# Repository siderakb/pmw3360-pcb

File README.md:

# PMW3360 PCB

| 2.54mm Pin Header                                                                                     | 0.5mm FFC/FPC                                                                                         |
| ----------------------------------------------------------------------------------------------------- | ----------------------------------------------------------------------------------------------------- |
|  |  |

[PixArt PMW3360DM-T2QU](https://www.pixart.com/products-detail/10/PMW3360DM-T2QU) optical mouse sensor breakout board, can be operated with either a 1.8V or 3.3V voltage level.  
Also look at [PMW3610 PCB](https://github.com/siderakb/pmw3610-pcb).

[Demo video 1](https://youtu.be/orrze81mV_8?t=312), [Demo video 2](https://youtu.be/CSA7Ih7nAls?si=umx-Psb8-lRDeviu)

## PCB

Online preview available [here](https://kicanvas.org/?github=https%3A%2F%2Fgithub.com%2Fsiderakb%2Fpmw3360-pcb%2Ftree%2Fmain%2Fpmw3360_pcb_pinheader), powered by [KiCanvas](https://github.com/theacodes/kicanvas).

### BOM

| Ref  | Value         | Footprint             |
| ---- | ------------- | --------------------- |
| C1   | 4.7uF/10V     | SMD 0603              |
| C2   | 100nF         | SMD 0603              |
| C3   | 1uF           | SMD 0603              |
| C4\* | 1uF           | SMD 0603              |
| C5\* | *DNI*         | SMD 0603              |
| R1\* | *DNI* or 10kΩ | SMD 0603              |
| R2   | 10kΩ          | SMD 0603              |
| R3   | 39Ω           | SMD 0603              |
| R4\* | *DNI*         | SMD 0603              |
| U1   | PMW3360       | PMW3360DM-T2QU 16 Pin |
| U2\* | TLV74318PDBVR | SOT-23-5              |
| J1\* | 8 Pin         |                       |

- *DNI*: don't install.
- SMD 0603 (Imperial) aka 1608 Metric.
- PMW3360 needs to be used with LM19-LSI lens.
- `R1` is optional/additional RESET pull up resistor, RESET pin of PMW3360 has a built in weak pull up circuit.
- `J1` connector have the following options:
    - 2.54mm pin header: [`pmw3360_pcb_pinheader/`](/pmw3360_pcb_pinheader/)
    - 0.5mm FFC/FPC: [`pmw3360_pcb_ffc/`](/pmw3360_pcb_ffc/)
    - JST GH 1.25mm: [`pmw3360_pcb_jst/`](/pmw3360_pcb_jst/)
- `U2` LDO regulator have the following options:

|  Ref  | Default       | Alt.           | Alt.        |
| :---: | ------------- | -------------- | ----------- |
|  U2   | TLV74318PDBVR | RT9193-18GB    | TPS73601DBV |
|  C4   | 1uF           | 1uF            | 4.7uF       |
|  C5   | *DNI*         | 22nF or larger | 56.2k**Ω**  |
|  R4   | *DNI*         | *DNI*          | 28kΩ        |
| Note  | Fixed 1.8V    | Fixed 1.8V     | Adj. 1.8V   |

### PCB Dimensions & Characteristics

Please refer to:
- 2.54mm pin header: [`pmw3360_pcb_pinheader/`](/pmw3360_pcb_pinheader/)
- 0.5mm FFC/FPC: [`pmw3360_pcb_ffc/`](/pmw3360_pcb_ffc/)
- JST GH 1.25mm: [`pmw3360_pcb_jst/`](/pmw3360_pcb_jst/)

> PCB sizes vary among different connector editions.

## Power

### Voltage-Level Config

3 configs available:

|          |   3.3V    |    1.8 with LDO     |         1.8V without LDO          |
| -------- | :-------: | :-----------------: | :-------------------------------: |
| VIN Typ. |   3.3V    | (VDD + 0.2V) ~ 5.5V |               1.8V                |
| VIN Max. |   3.6V    |        5.5V         |               2.1V                |
| JP1      | `[1-2 3]` |      `[1 2-3]`      |             `[1-2-3]`             |
| Note     |           |                     | `U2`, `R4`, `C3~5` can be omitted |

### Jumper

| JP1 Config |                     | Description                  |
| :--------: | ------------------- | ---------------------------- |
| `[1-2 3]`  | 2 and 1 close, 3 NC | VIO = VIN                    |
| `[1 2-3]`  | 2 and 3 close, 1 NC | VIO = VDD (i.e. LDO output)  |
| `[1-2-3]`  | 1, 2 and 3 close    | VIO = VDD = VIN (LDO bypass) |

### Operating Voltage Range

- **VDD**: 1.8 ~ 2.1V (i.e. LDO Vout)
- **VIO**: VDD ~ 3.6V (i.e. VDDIO)
- **VIN**: Depends on [Voltage-Level config](#voltage-level-config)

## Firmware Examples

- QMK
    - [RP2040](/firmware/qmk/pmw3360_rp2040/)
    - [Pro Micro](/firmware/qmk/pmw3360_promicro/)
- [nRF Connect SDK (NCS)](/firmware/nordic/)

Pre-Build firmware can be found in [Releases](https://github.com/siderakb/pmw3360-pcb/releases/tag/fw_v0.1.0).

## License

- KiCad files (e.g. schematics, PCBs, footprints and symbols): [CERN-OHL-P v2](/LICENSE-CERN-OHL-P).
- `firmware/qmk/`: [GPL v2](/LICENSE-QMK).
- `firmware/nordic/`: [Nordic-5-Clause](/LICENSE-Nordic).

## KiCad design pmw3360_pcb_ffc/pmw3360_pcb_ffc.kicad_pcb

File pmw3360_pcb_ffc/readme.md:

# PMW3360 PCB FFC/FPC Connector

- `J1`: 0.5mm 8pin FFC/FPC connector (AFC01-S08FCA-00).
- Mounting holes: 4x M2 (∅2.2mm).

## PCB Characteristics

- Copper layer count: 2
- Board overall dimensions: 27 mm x 22.5 mm
- Min track/spacing: 0.2 mm / 0.2 mm
- Min hole diameter: 0.3 mm
- Castellated pads: No
- Plated board edge: No
- Edge card connectors: No

## Changelog

### [F.1.0] - 2023-12-15

- Changed LDO from TPS73601DBV to TLV74318PDBVR.
- Changed R5 to C5.

### [F.0.0] - 2023-06-29

- Reduce the board size to 27 x 22.5 mm.
- Update PWM3360 footprint (reduce the size of the pads).

### [3.1.0] - 2023-05-27

- First FFC/FPC edition release.

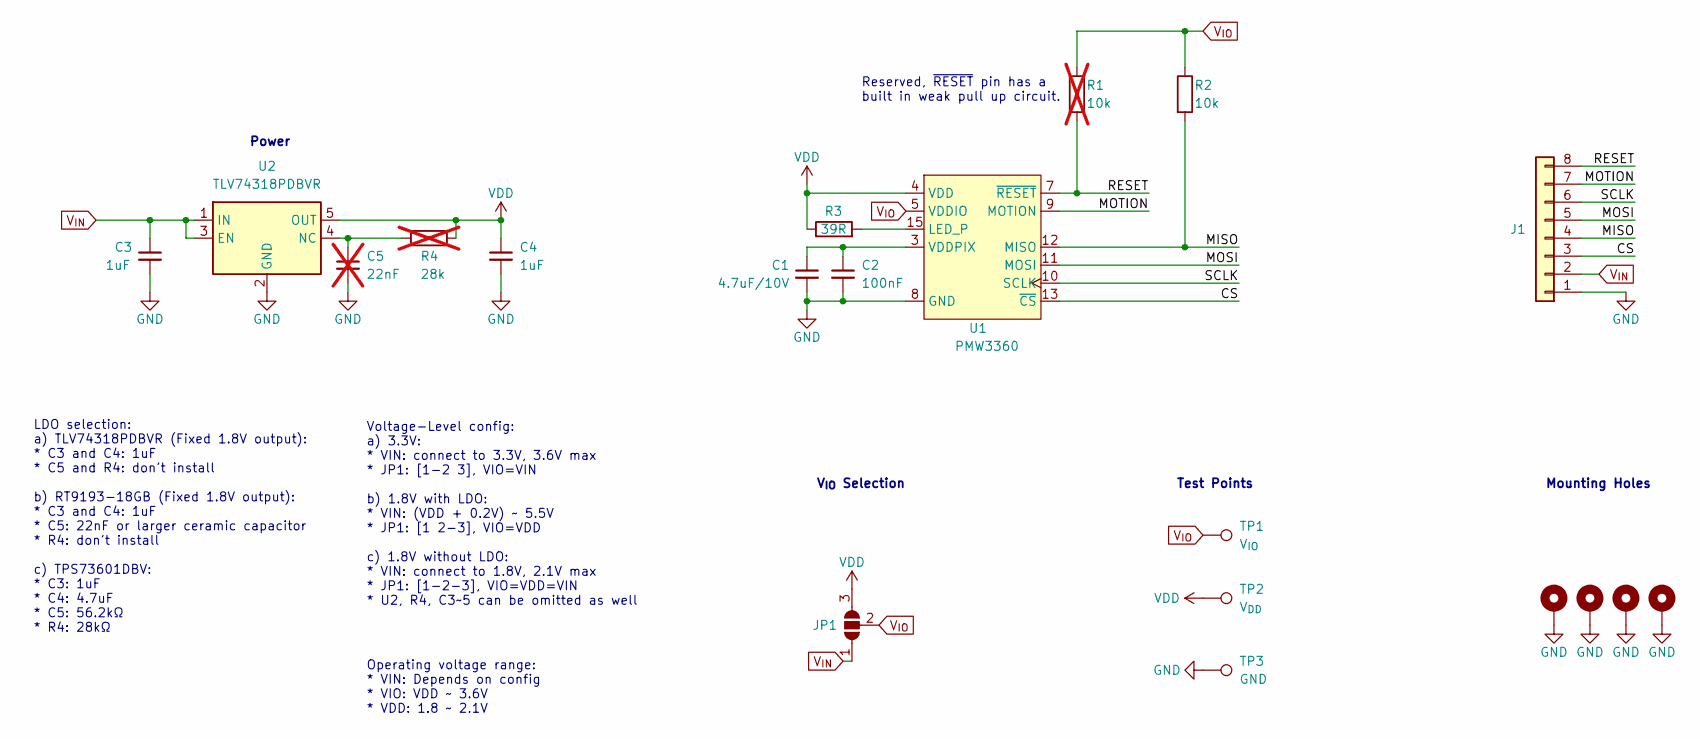
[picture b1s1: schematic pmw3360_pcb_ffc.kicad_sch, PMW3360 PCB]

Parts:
C1: 4.7uF/10V; C_0603_1608Metric_Pad1.08x0.95mm_HandSolder
C2: 100nF; C_0603_1608Metric_Pad1.08x0.95mm_HandSolder
C3, C4: 1uF; C_0603_1608Metric_Pad1.08x0.95mm_HandSolder
C5: 22nF; C_0603_1608Metric_Pad1.08x0.95mm_HandSolder; Mfr. # CL10B223KB8NNNC; LCSC C21122; not fitted
H1, H2, H3, H4: MountingHole_Pad; MountingHole_2.2mm_M2_ISO14580_Pad
J1: Interface; FPC_8P_0.5mm_AFC01-S08FCA-00
JP1: SolderJumper_3_Open; SolderJumper-3_P1.3mm_Open_RoundedPad1.0x1.5mm_NumberLabels
R1: 10k; R_0603_1608Metric_Pad0.98x0.95mm_HandSolder; not fitted
R2: 10k; R_0603_1608Metric_Pad0.98x0.95mm_HandSolder
R3: 39R; R_0603_1608Metric_Pad0.98x0.95mm_HandSolder
R4: 28k; R_0603_1608Metric_Pad0.98x0.95mm_HandSolder; not fitted
TP1: V_{IO}; TestPoint_Pad_D1.0mm
TP2: V_{DD}; TestPoint_Pad_D1.0mm
TP3: GND; TestPoint_Pad_D1.0mm
U1: PMW3360; PMW3360DM-T2QU 16Pin
U2: TLV74318PDBVR; SOT-23-5; Mfr. # TLV74318PDBVR; LCSC C485152

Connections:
/CS: J1.3, U1.13 (~CS)
/MISO: J1.4, R2.2, U1.12 (MISO)
/MOSI: J1.5, U1.11 (MOSI)
/MOTION: J1.7, U1.9 (MOTION)
/RESET: J1.8, R1.2, U1.7 (~RESET)
/SCLK: J1.6, U1.10 (SCLK)
GND: C1.2, C2.2, C3.2, C4.2, C5.2, H1.1, H2.1, H3.1, H4.1, J1.1, TP3.1, U1.8 (GND), U2.2 (GND)
unnamed: R3.2, U1.15 (LED_P)
unnamed: C1.1, C2.1, U1.3 (VDDPIX)
unnamed: C5.1, R4.2, U2.4 (NC)
VDD: C4.1, JP1.3 (B), R3.1, R4.1, TP2.1, U1.4 (VDD), U2.5 (OUT)
V_{IN}: C3.1, J1.2, JP1.1 (A), U2.1 (IN), U2.3 (EN)
V_{IO}: JP1.2 (C), R1.1, R2.1, TP1.1, U1.5 (VDDIO)

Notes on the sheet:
Reserved, ~{RESET} pin has a built in weak pull up circuit.
V_{IO} Selection
Mounting Holes
Power
Test Points
LDO selection: a) TLV74318PDBVR (Fixed 1.8V output): * C3 and C4: 1uF * C5 and R4: don't install b) RT9193-18GB (Fixed 1.8V output): * C3 and C4: 1uF * C5: 22nF or larger ceramic capacitor * R4: don't install c) TPS73601DBV: * C3: 1uF * C4: 4.7uF * C5: 56.2kΩ * R4: 28kΩ
Operating voltage range: * VIN: Depends on config * VIO: VDD ~ 3.6V * VDD: 1.8 ~ 2.1V
Voltage-Level config: a) 3.3V: * VIN: connect to 3.3V, 3.6V max * JP1: [1-2 3], VIO=VIN b) 1.8V with LDO: * VIN: (VDD + 0.2V) ~ 5.5V * JP1: [1 2-3], VIO=VDD c) 1.8V without LDO: * VIN: connect to 1.8V, 2.1V max * JP1: [1-2-3], VIO=VDD=VIN * U2, R4, C3~5 can be omitted as well

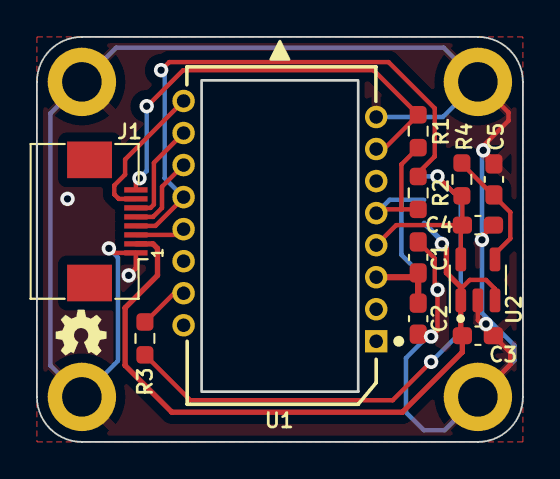
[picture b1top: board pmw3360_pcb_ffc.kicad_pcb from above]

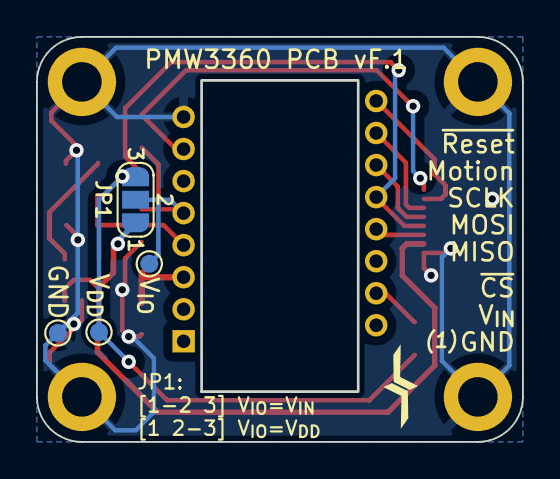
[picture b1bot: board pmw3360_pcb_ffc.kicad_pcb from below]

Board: 2 copper layers, 27.0 x 22.5 mm, 20 parts (4 on the bottom side), 13 nets.

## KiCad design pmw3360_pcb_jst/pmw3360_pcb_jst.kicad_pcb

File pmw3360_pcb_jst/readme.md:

# PMW3360 PCB JST GH Connector

- `J1`: JST GH 1.25mm connector (SM08B-GHS-TB(LF)(SN)).
- Mounting holes: 4x M2 (∅2.2mm).

## PCB Characteristics

- Copper layer count: 2
- Board overall dimensions: 27 mm x 28 mm
- Min track/spacing: 0.2 mm / 0.2 mm
- Min hole diameter: 0.3 mm
- Castellated pads: No
- Plated board edge: No
- Edge card connectors: No

## Changelog

### [J.1.0] - 2023-12-15

- Changed LDO from TPS73601DBV to TLV74318PDBVR.
- Changed R5 to C5.

### [J.0.0] - 2023-06-29

- Update PWM3360 footprint (reduce the size of the pads).

### [3.0.0] - 2023-05-27

- First JST edition release.

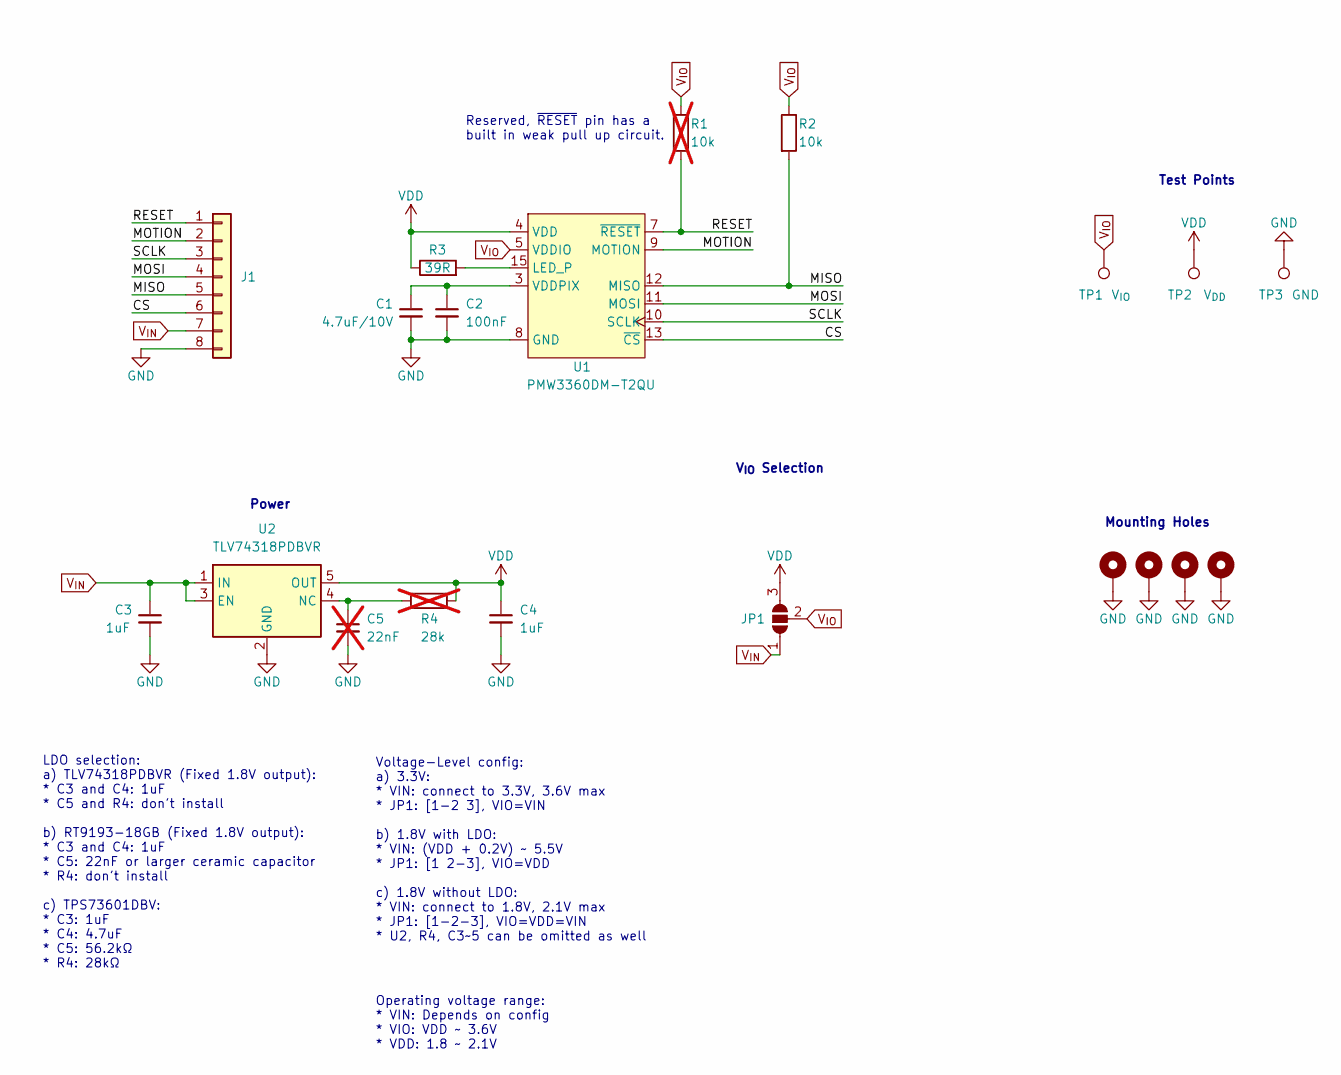
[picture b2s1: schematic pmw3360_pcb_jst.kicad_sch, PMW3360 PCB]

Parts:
C1: 4.7uF/10V; C_0603_1608Metric_Pad1.08x0.95mm_HandSolder
C2: 100nF; C_0603_1608Metric_Pad1.08x0.95mm_HandSolder
C3, C4: 1uF; C_0603_1608Metric_Pad1.08x0.95mm_HandSolder
C5: 22nF; C_0603_1608Metric_Pad1.08x0.95mm_HandSolder; Mfr. # CL10B223KB8NNNC; LCSC C21122; not fitted
H1, H2, H3, H4: MountingHole_Pad; MountingHole_2.2mm_M2_ISO14580_Pad
J1: Conn_01x08; JST_GH_SM08B-GHS-TB_1x08-1MP_P1.25mm_Horizontal
JP1: SolderJumper_3_Open; SolderJumper-3_P1.3mm_Open_RoundedPad1.0x1.5mm_NumberLabels
R1: 10k; R_0603_1608Metric_Pad0.98x0.95mm_HandSolder; not fitted
R2: 10k; R_0603_1608Metric_Pad0.98x0.95mm_HandSolder
R3: 39R; R_0603_1608Metric_Pad0.98x0.95mm_HandSolder
R4: 28k; R_0603_1608Metric_Pad0.98x0.95mm_HandSolder; not fitted
TP1: V_{IO}; TestPoint_Pad_D1.0mm
TP2: V_{DD}; TestPoint_Pad_D1.0mm
TP3: GND; TestPoint_Pad_D1.0mm
U1: PMW3360DM-T2QU; PMW3360DM-T2QU 16Pin
U2: TLV74318PDBVR; SOT-23-5; Mfr. # TLV74318PDBVR; LCSC C485152

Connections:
/CS: J1.6, U1.13 (~CS)
/MISO: J1.5, R2.2, U1.12 (MISO)
/MOSI: J1.4, U1.11 (MOSI)
/MOTION: J1.2, U1.9 (MOTION)
/RESET: J1.1, R1.2, U1.7 (~RESET)
/SCLK: J1.3, U1.10 (SCLK)
GND: C1.2, C2.2, C3.2, C4.2, C5.2, H1.1, H2.1, H3.1, H4.1, J1.8, TP3.1, U1.8 (GND), U2.2 (GND)
unnamed: R3.2, U1.15 (LED_P)
unnamed: C1.1, C2.1, U1.3 (VDDPIX)
unnamed: C5.1, R4.2, U2.4 (NC)
VDD: C4.1, JP1.3 (B), R3.1, R4.1, TP2.1, U1.4 (VDD), U2.5 (OUT)
V_{IN}: C3.1, J1.7, JP1.1 (A), U2.1 (IN), U2.3 (EN)
V_{IO}: JP1.2 (C), R1.1, R2.1, TP1.1, U1.5 (VDDIO)

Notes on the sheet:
Mounting Holes
Test Points
V_{IO} Selection
LDO selection: a) TLV74318PDBVR (Fixed 1.8V output): * C3 and C4: 1uF * C5 and R4: don't install b) RT9193-18GB (Fixed 1.8V output): * C3 and C4: 1uF * C5: 22nF or larger ceramic capacitor * R4: don't install c) TPS73601DBV: * C3: 1uF * C4: 4.7uF * C5: 56.2kΩ * R4: 28kΩ
Operating voltage range: * VIN: Depends on config * VIO: VDD ~ 3.6V * VDD: 1.8 ~ 2.1V
Power
Reserved, ~{RESET} pin has a built in weak pull up circuit.
Voltage-Level config: a) 3.3V: * VIN: connect to 3.3V, 3.6V max * JP1: [1-2 3], VIO=VIN b) 1.8V with LDO: * VIN: (VDD + 0.2V) ~ 5.5V * JP1: [1 2-3], VIO=VDD c) 1.8V without LDO: * VIN: connect to 1.8V, 2.1V max * JP1: [1-2-3], VIO=VDD=VIN * U2, R4, C3~5 can be omitted as well

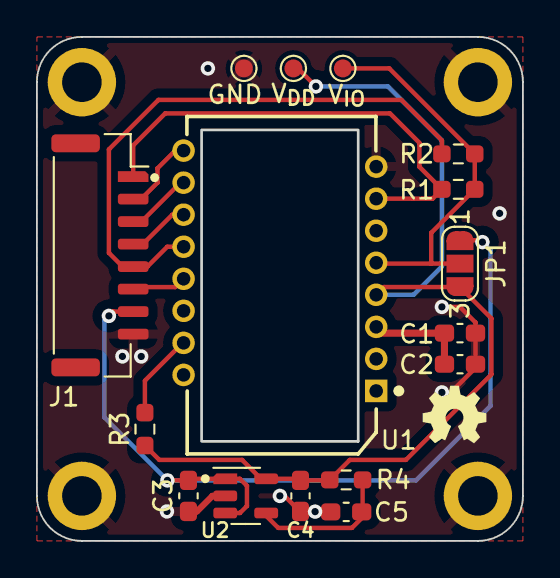
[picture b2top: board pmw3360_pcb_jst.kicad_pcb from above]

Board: 2 copper layers, 27.0 x 28.0 mm, 20 parts (0 on the bottom side), 13 nets.

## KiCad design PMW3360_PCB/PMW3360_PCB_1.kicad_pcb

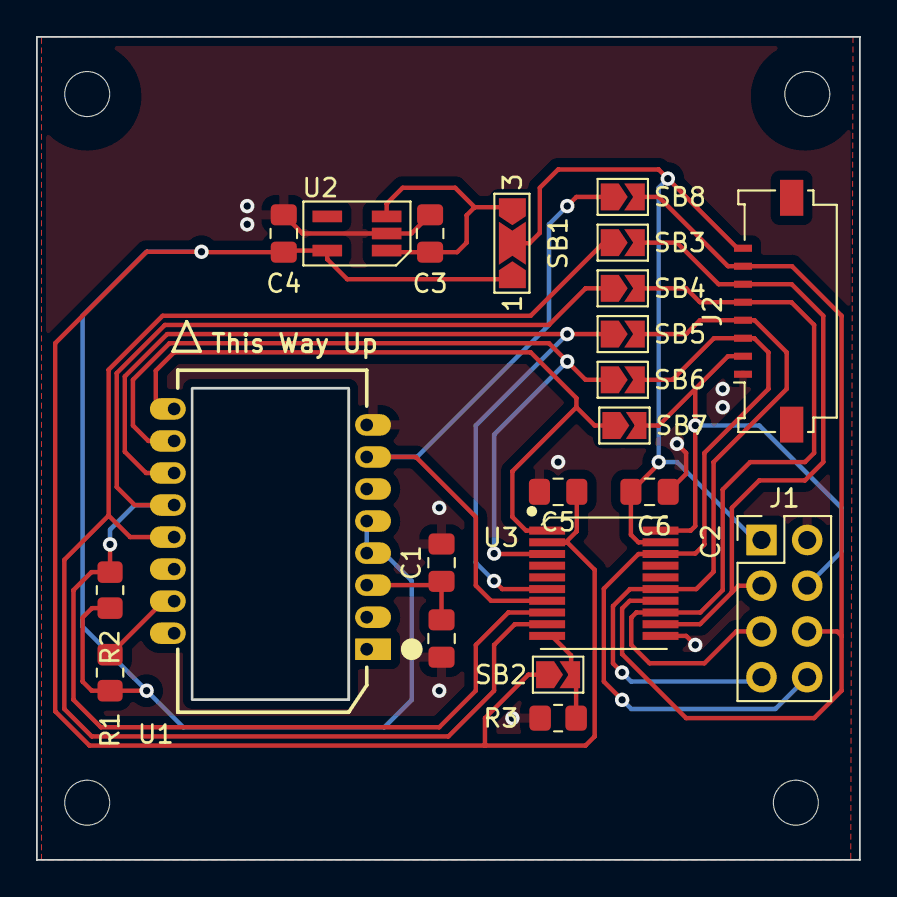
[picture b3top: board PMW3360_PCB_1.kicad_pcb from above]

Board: 2 copper layers, 45.7 x 45.7 mm, 22 parts (0 on the bottom side), 19 nets.

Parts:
C1: 4.7uF/10V; C_0805_2012Metric_Pad1.18x1.45mm_HandSolder
C2: 100nF; C_0805_2012Metric_Pad1.18x1.45mm_HandSolder
C3, C4, C5, C6: 1uF; C_0805_2012Metric_Pad1.18x1.45mm_HandSolder
J1: Conn_02x04_Top_Bottom; PinHeader_2x04_P2.54mm_Vertical
J2: Conn_01x08_MountingPin; Molex_200528-0080_1x08-1MP_P1.00mm_Horizontal
R1: 39R; R_0805_2012Metric_Pad1.20x1.40mm_HandSolder
R2, R3: 10k; R_0805_2012Metric_Pad1.20x1.40mm_HandSolder
SB1: SolderJumper_3_Bridged12; SolderJumper-3_P2.0mm_Open_TrianglePad1.0x1.5mm_NumberLabels
SB2, SB3, SB4, SB5, SB6, SB7, SB8: SolderJumper_2_Open; SolderJumper-2_P1.3mm_Open_TrianglePad1.0x1.5mm
U1: PMW3360DM-T2QU; 16pin‐DIP(PMW3360DM-T2QU)
U2: AP7331-20WG-7; SOT-25-5_Handsoldering
U3: TXS0108E-QPWRQ1; TSSOP-20

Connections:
/CS: SB3.1 (A), U1.13 (CS), U3.9 (A8)
/CS_O: J1.3, J2.6, SB3.2 (B), U3.12 (B8)
/MISO: R2.2, SB4.1 (A), U1.12 (MISO), U3.8 (A7)
/MISO_O: J1.5, J2.5, SB4.2 (B), U3.13 (B7)
/MOSI: SB5.1 (A), U1.11 (MOSI), U3.6 (A5)
/MOSI_O: J1.7, J2.4, SB5.2 (B), U3.15 (B5)
/MOTION: SB7.1 (A), U1.9 (MOTION), U3.1 (A1)
/MOTION_O: J1.4, J2.2, SB7.2 (B), U3.20 (B1)
/RESET: SB8.1 (A), U1.7 (RESET), U3.7 (A6)
/RESET_O: J1.6, J2.7, SB8.2 (B), U3.14 (B6)
/SCLK: SB6.1 (A), U1.10 (SCLK), U3.3 (A2)
/SCLK_O: J1.8, J2.3, SB6.2 (B), U3.18 (B2)
/V_IN: C6.1, J1.1, J2.8, SB1.2 (C), U3.19 (VCCB)
GND: C1.2, C2.2, C3.2, C4.2, C5.2, C6.2, J1.2, J2.1, R3.2, U1.8 (GND), U2.2 (GND), U3.11 (GND)
unnamed: C3.1, SB1.3 (B), U2.1 (IN), U2.3 (EN)
unnamed: R3.1, SB2.2 (B), U3.10 (OE)
unnamed: C1.1, C2.1, U1.3 (VDDPIX)
unnamed: R1.2, U1.15 (LED_P)
VDD: C4.1, C5.1, R1.1, R2.1, SB1.1 (A), SB2.1 (A), U1.4 (VDD), U1.5 (VDDIO), U2.5 (OUT), U3.2 (VCCA)

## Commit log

2022-08-20 Add KiCAD files
2022-10-13 Remove unused file
2022-10-13 Add license info
2022-10-14 Update power net name
2022-10-14 Add mounting hole dimension
2022-10-20 Deleted unconnect end track
2023-02-01 Update date
2023-02-26 Replace JST GH 1.25 connector with 0.5mm FPC
2023-04-29 Update `.gitignore`
2023-04-29 Add footprint and symbol library path table
2023-04-29 Add firmware examples
2023-04-29 Update firmware examples path
2023-04-29 Reduce board size
2023-06-25 Update URL, replace "ziteh" with "siderakb".
2023-06-28 Update schematic
2023-06-28 Rerounted
2023-06-29 Add sheet comments
2023-06-29 Rename Rev3 to 'pmw3360_pcb_ffc'
2023-06-29 Add v3.0 back
2023-06-29 Add rev2 back
2023-06-29 Add muti license
2023-06-29 Update README.md for license
2023-06-29 Update symbol references
2023-06-29 Update silkscreen text
2023-06-29 Add FFC readme.md
2023-06-29 Add JST readme.md
2023-06-29 Modify PinHeader Rev from `2.2` to `P.0`
2023-06-29 Fix url
2023-06-29 Fix typo
2023-06-29 Add KiCanvas online preview link
2023-07-17 Fix path
2023-10-07 Change pin header edition LDO to TLV74318PDBVR
2023-11-14 Change hardware license to CERN-OHL-P v2
2023-12-15 Add SPI clock setting
2023-12-15 Update designators
2024-01-28 Update NCS firmware
2024-05-28 Update issue templates

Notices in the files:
README.md:
License: CERN-OHL-P v2
pmw3360_pcb_ffc/pmw3360_pcb_ffc.kicad_pcb:
Open Source Hardware, CERN-OHL-P v2
